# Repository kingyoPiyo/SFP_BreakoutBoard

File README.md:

# SFP_BreakoutBoard
KiCad とプリント基板発注練習用に作成した SFP 用の Breakout Board です。身近にある Type-C ケーブルから給電可能となるように仕上げてみました。取り付け穴位置は秋月電子のCタイプ基板に揃えているためスタック可能です。  
性能をテストできる機材を持ち合わせていないので信号品質等の詳細はスペック不明ですが、SFP → SMA → SFP 接続時に 1Gbps および 10Gbps で送受信可能なことを確認しています。  

# 開発環境
- KiCad Version 5.1.6
- RF-tools-KICAD https://github.com/easyw/RF-tools-KiCAD

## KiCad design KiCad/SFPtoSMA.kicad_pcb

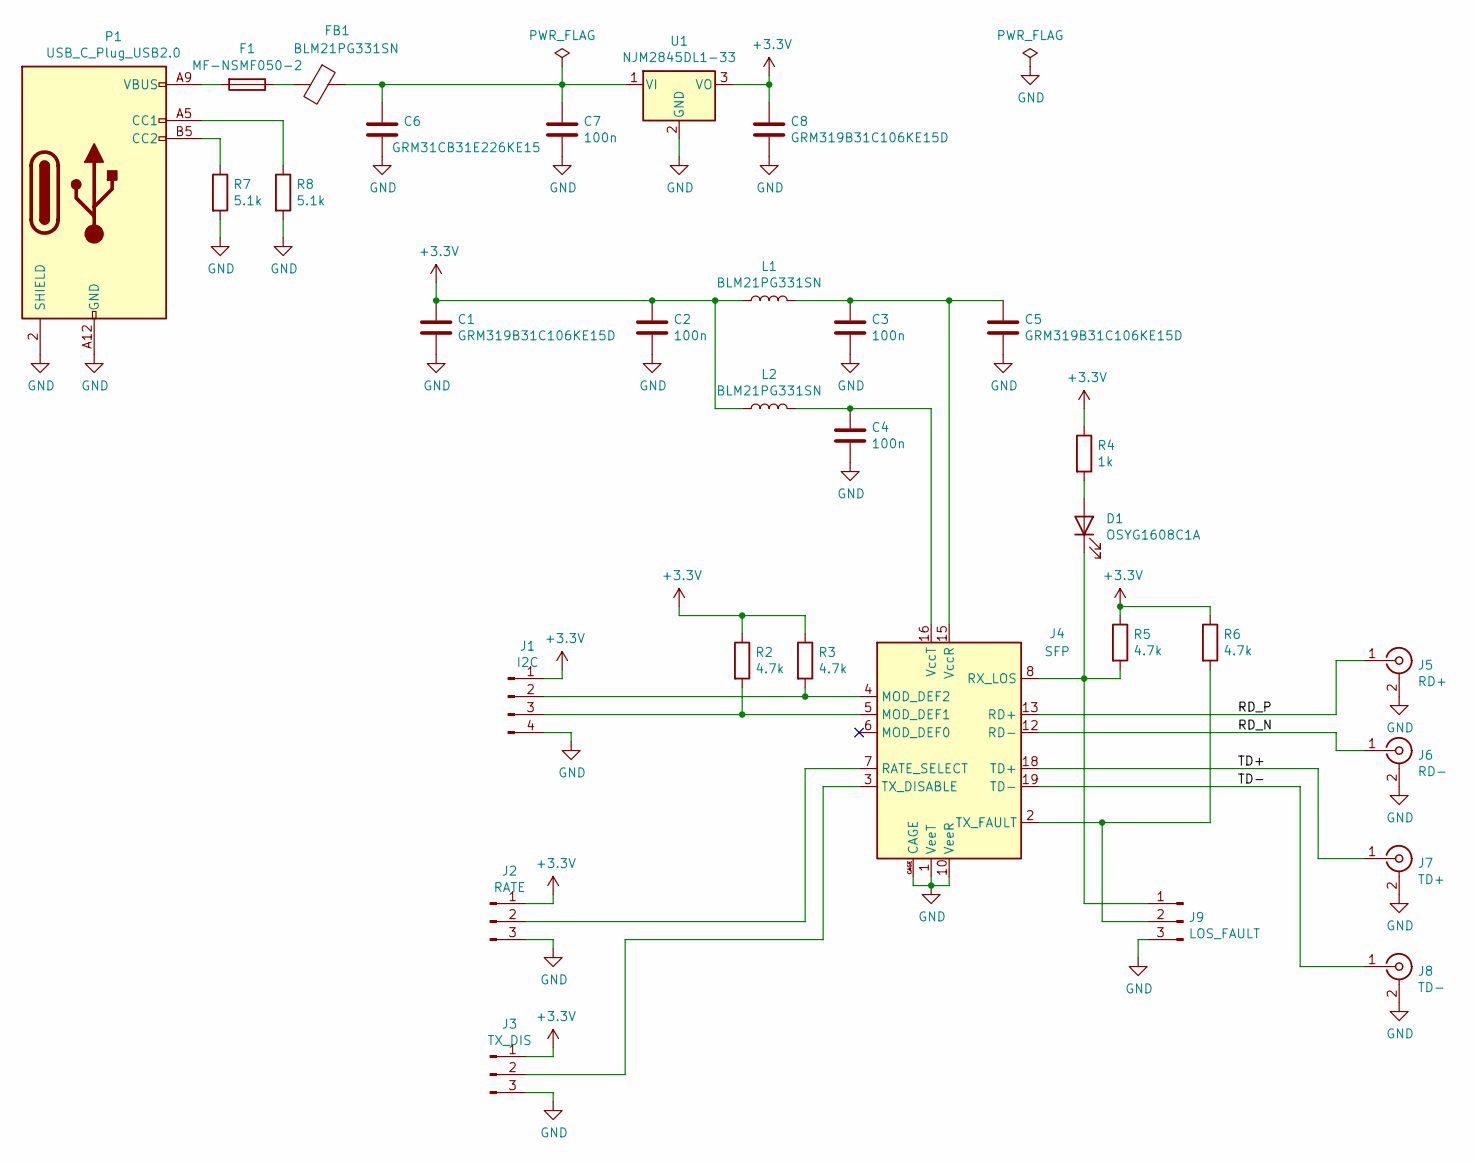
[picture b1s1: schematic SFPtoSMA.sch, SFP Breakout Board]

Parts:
C1, C5, C8: GRM319B31C106KE15D; C_1206_3216Metric
C2, C3, C4, C7: 100n; C_0603_1608Metric
C6: GRM31CB31E226KE15; C_1206_3216Metric
D1: OSYG1608C1A; LED_0603_1608Metric
F1: MF-NSMF050-2; Fuse_1210_3225Metric
FB1: BLM21PG331SN; L_0805_2012Metric
J1: I2C; PinHeader_1x04_P2.54mm_Vertical
J2: RATE; PinHeader_1x03_P2.54mm_Vertical
J3: TX_DIS; PinHeader_1x03_P2.54mm_Vertical
J4: SFP; Connector_SFP_and_Cage
J5: RD+; SMA_Samtec_SMA-J-P-X-ST-EM1_EdgeMount
J6: RD-; SMA_Samtec_SMA-J-P-X-ST-EM1_EdgeMount
J7: TD+; SMA_Samtec_SMA-J-P-X-ST-EM1_EdgeMount
J8: TD-; SMA_Samtec_SMA-J-P-X-ST-EM1_EdgeMount
J9: LOS_FAULT; PinHeader_1x03_P2.54mm_Vertical
L1, L2: BLM21PG331SN; L_0805_2012Metric
P1: USB_C_Plug_USB2.0; USB-C_Power_only
R2, R3, R5, R6: 4.7k; R_0603_1608Metric
R4: 1k; R_0603_1608Metric
R7, R8: 5.1k; R_0603_1608Metric
U1: NJM2845DL1-33; TO-252-2

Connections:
+3V3: C1.1, C2.1, C8.1, J1.1, J2.1, J3.1, L1.1, L2.1, R2.1, R3.1, R4.1, R5.1, R6.1, U1.3 (VO)
/RD_N: J4.12 (RD-), J6.1 (In)
/RD_P: J4.13 (RD+), J5.1 (In)
/TD+: J4.18 (TD+), J7.1 (In)
/TD-: J4.19 (TD-), J8.1 (In)
GND: C1.2, C2.2, C3.2, C4.2, C5.2, C6.2, C7.2, C8.2, J1.4, J2.3, J3.3, J4.1 (VeeT), J4.9 (VeeR), J4.10 (VeeR), J4.11 (VeeR), J4.14 (VeeR), J4.17 (VeeT), J4.20 (VeeT), J4.CAGE, J5.2 (Ext), J6.2 (Ext), J7.2 (Ext), J8.2 (Ext), J9.3, P1.2 (SHIELD), P1.A12 (GND), P1.B12 (GND), R7.2, R8.2, U1.2 (GND)
unnamed: C3.1, C5.1, J4.15 (VccR), L1.2
unnamed: C4.1, J4.16 (VccT), L2.2
unnamed: C6.1, C7.1, FB1.1, U1.1 (VI)
unnamed: D1.1 (K), J4.8 (RX_LOS), J9.1, R5.2
unnamed: D1.2 (A), R4.2
unnamed: F1.1, FB1.2
unnamed: F1.2, P1.A9 (VBUS), P1.B9 (VBUS)
unnamed: J1.2, J4.4 (MOD_DEF2), R3.2
unnamed: J1.3, J4.5 (MOD_DEF1), R2.2
unnamed: J2.2, J4.7 (RATE_SELECT)
unnamed: J3.2, J4.3 (TX_DISABLE)
unnamed: J4.2 (TX_FAULT), J9.2, R6.2
unnamed: P1.A5 (CC1), R8.1
unnamed: P1.B5 (CC2), R7.1

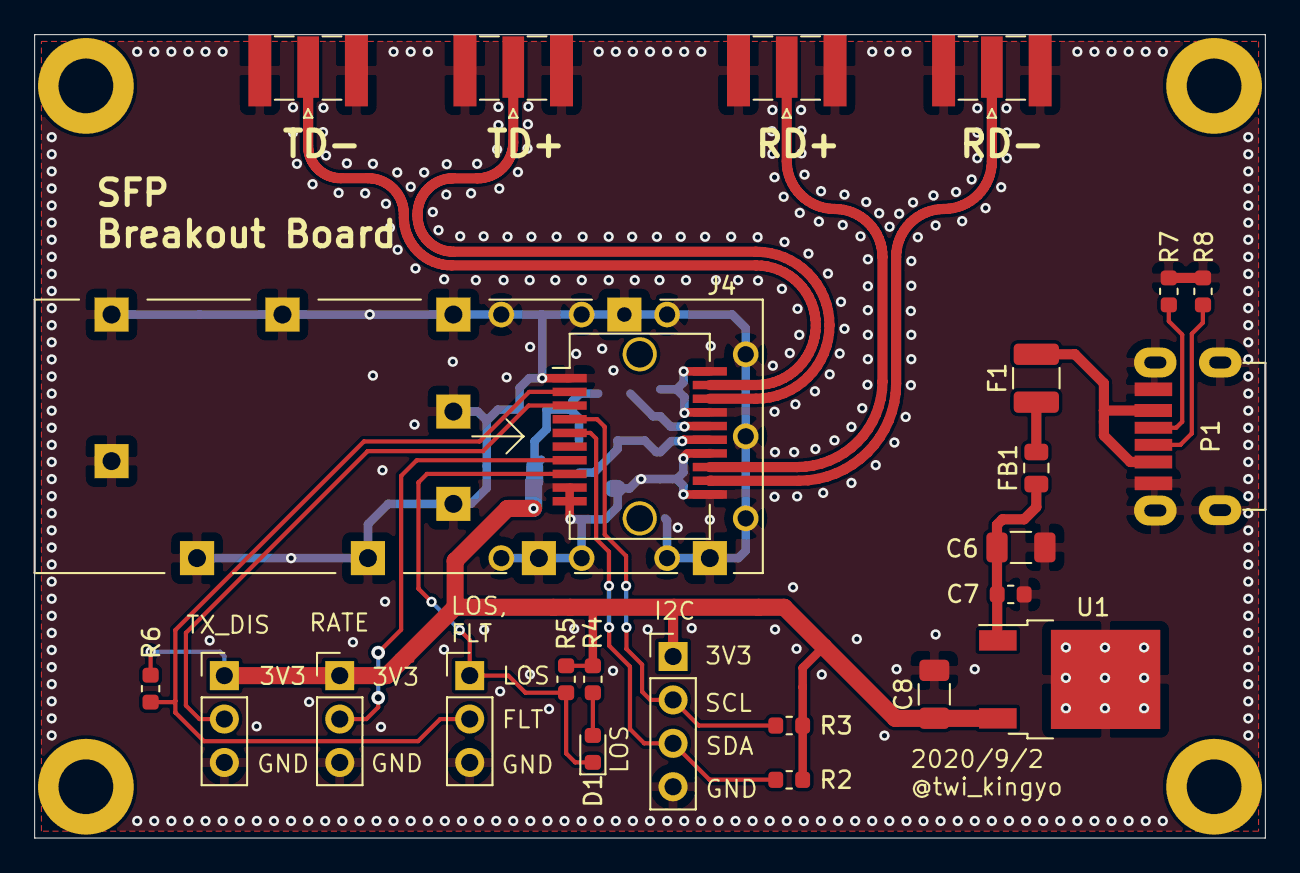
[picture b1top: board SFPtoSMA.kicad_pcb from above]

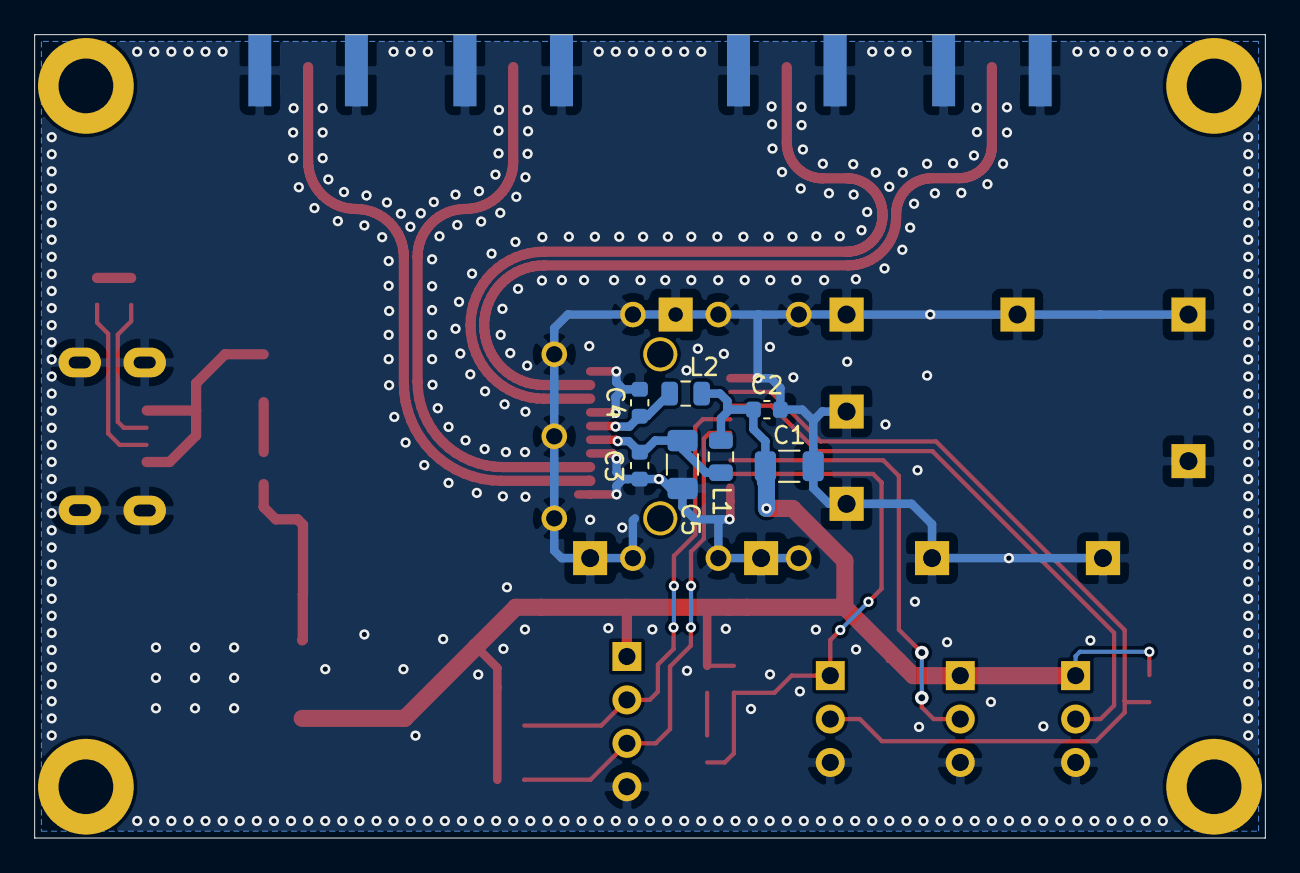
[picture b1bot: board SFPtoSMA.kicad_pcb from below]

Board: 2 copper layers, 72.0 x 47.0 mm, 31 parts (7 on the bottom side), 20 nets.

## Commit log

2022-02-03 move files
